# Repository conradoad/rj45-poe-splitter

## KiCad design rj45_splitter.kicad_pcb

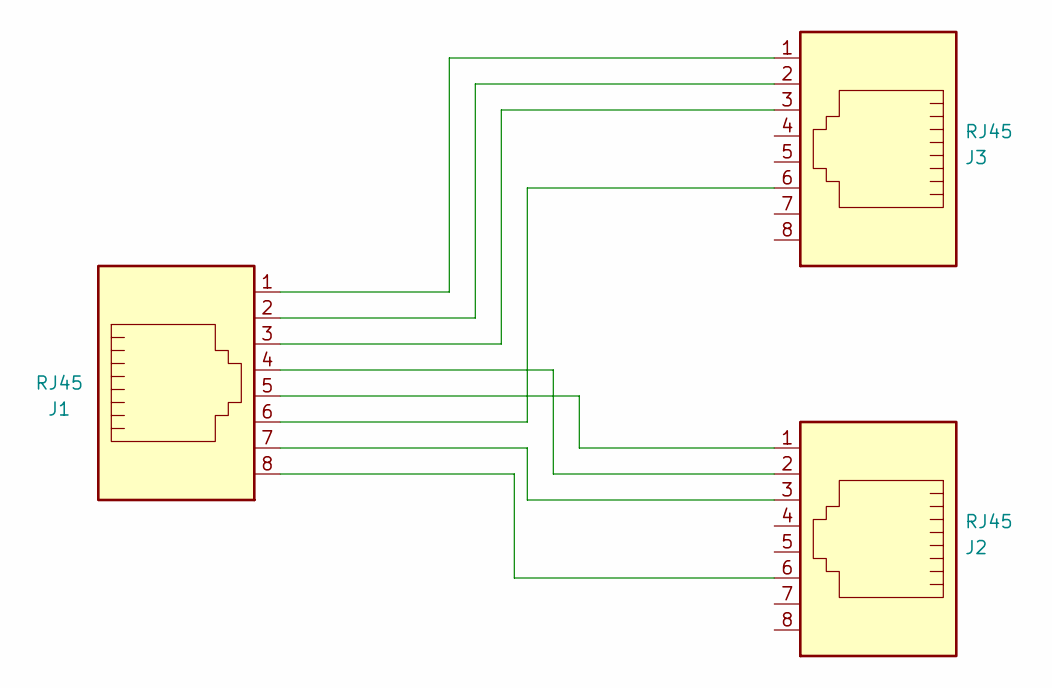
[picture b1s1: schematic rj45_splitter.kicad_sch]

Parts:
J1, J2, J3: RJ45; RJ45_YH-55-05

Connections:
unnamed: J1.1, J3.1
unnamed: J1.2, J3.2
unnamed: J1.3, J3.3
unnamed: J1.4, J2.2
unnamed: J1.5, J2.1
unnamed: J1.6, J3.6
unnamed: J1.7, J2.3
unnamed: J1.8, J2.6

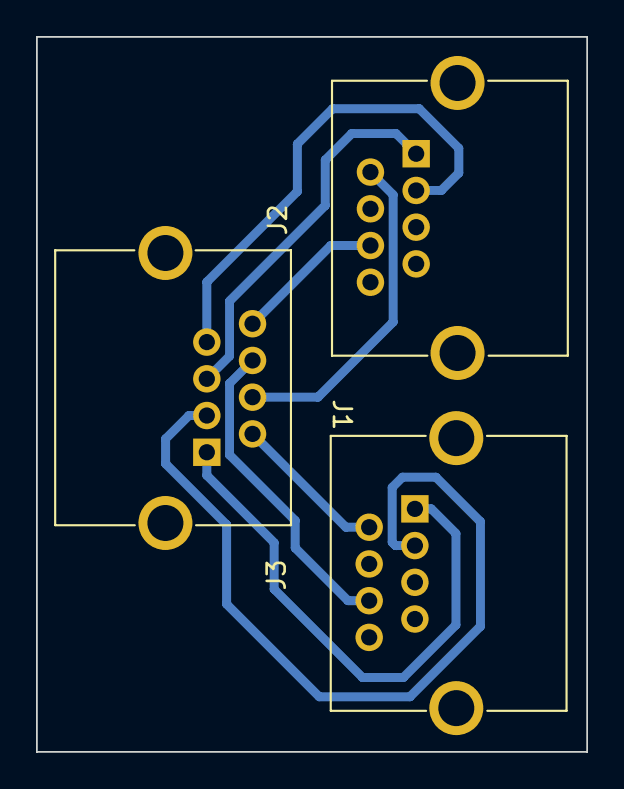
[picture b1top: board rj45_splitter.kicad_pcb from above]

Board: 2 copper layers, 30.6 x 39.7 mm, 3 parts (0 on the bottom side), 8 nets.

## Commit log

2022-10-16 First commig
2024-12-16 commit before system update
